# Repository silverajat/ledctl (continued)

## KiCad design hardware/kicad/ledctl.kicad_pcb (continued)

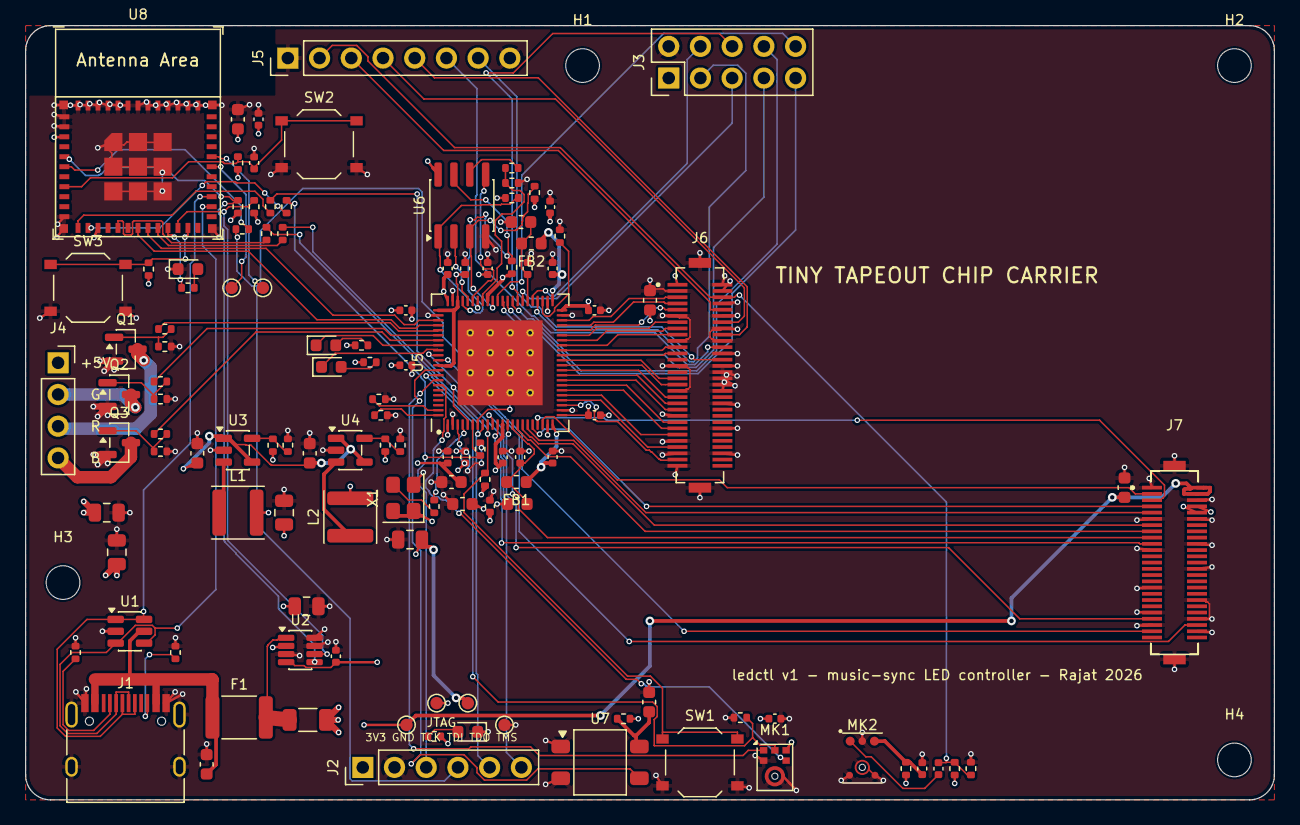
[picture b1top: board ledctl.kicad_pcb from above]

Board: 4 copper layers, 100.0 x 62.0 mm, 123 parts (0 on the bottom side), 112 nets.

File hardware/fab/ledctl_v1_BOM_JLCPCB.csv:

Comment,Designator,Footprint,LCSC Part #
10u,"C1,C4,C6,C34,C35,C36",C_0603_1608Metric,C19702
4.7k,"R9,R10,R18,R19,R20,R25,R26,R27,R35,R36",R_0402_1005Metric,C25900
22u,"C3,C5,C7,C28,C29",C_0805_2012Metric,C45783
ESP32-C3-MINI-1-N4,U8,ESP32-C3-MINI-1,C2838502
100n,"C2,C9,C11,C12,C13,C14,C15,C17,C18,C19,C20,C21,C22,C23,C24,C26,C27,C30,C37",C_0402_1005Metric,C1525
100k,R28,R_0402_1005Metric,C25741
4.7u,"C8,C10,C16,C25,C31",C_0603_1608Metric,C19666
button TS-1187A,"SW1,SW2,SW3",SW_Push_1P1T_XKB_TS-1187A,C318884
USB-C (power + ESP32 USB),J1,USB_C_Receptacle_HRO_TYPE-C-31-M-12,C165948
0,R16,R_0402_1005Metric,C17168
10k,"R7,R13,R33,R34",R_0402_1005Metric,C25744
68k,R5,R_0402_1005Metric,C36871
1k,"R11,R12,R14,R15,R17,R42",R_0402_1005Metric,C11702
100,"R22,R23,R24,R29,R30,R37,R38,R39,R40,R41",R_0402_1005Metric,C25076
10m 1%,R3,R_1206_3216Metric,C601097
600R@100MHz,"FB1,FB2",L_0603_1608Metric,C1002
"LED strip (1=+5V black, 2=G, 3=R, 4=B)",J4,PinSocket_1x04_P2.54mm_Vertical,C2718488
USBLC6-2SC6,U1,SOT-23-6,C7519
SY8089AAAC,"U3,U4",SOT-23-5,C78988
AO3400A,"Q1,Q2,Q3",SOT-23,C20917
IRM-H638T/TR2,U7,Everlight_IRM-H6xxT,C91447
2.2k,R4,R_0402_1005Metric,C25879
1u,"C32,C33,C38",C_0402_1005Metric,C52923
MSM381A3729Z9E-C,MK2,MEMSensing_LGA-6_2.95x3.76mm,C51928206
2.2uH SWPA4030S2R2MT,"L1,L2",L_Sunlord_SWPA4030S,C36409
22,R21,R_0402_1005Metric,C25092
FPGA JTAG,J2,PinHeader_1x06_P2.54mm_Vertical,C42431790
W25Q16JVSNIQ,U6,SOIC-8_3.9x4.9mm_P1.27mm,C2456211
27MHz 3.3V CMOS,X1,Oscillator_SMD_Abracon_ASE-4Pin_3.2x2.5mm,C22434870
5.1k,"R1,R2",R_0402_1005Metric,C25905
INA219AIDCNR,U2,SOT-23-8,C87469
GW2AR-LV18QN88C8/I7,U5,QFN-88-1EP_10x10mm_P0.4mm_EP6.74x6.74mm,C380550
DF12NB(5.0)-60DP-0.5V(51),J6,Hirose_DF12NB5.0-60DP_TT,C2847989
15k,"R6,R8",R_0402_1005Metric,C25756
DF12NB(5.0)-50DP-0.5V(51),J7,Hirose_DF12NB5.0-50DP_TT,C3020266
2.6A hold / 5A trip,F1,Fuse_1812_4532Metric,C20814
ICS-43434,MK1,InvenSense_ICS-43434-6_3.5x2.65mm,C5656610
red LED KT-0603R,"D1,D2,D3,D4",LED_0603_1608Metric,C2286

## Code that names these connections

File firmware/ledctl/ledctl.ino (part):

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// FPGA does the I2S mic + beat detection and sends 'B' on every beat.
//
// Pins (ESP32-C3-MINI-1):
//   GPIO4 = UART TX -> FPGA pin 70      GPIO5 = UART RX <- FPGA pin 69
//   GPIO8 = I2C SDA, GPIO2 = I2C SCL   (INA219 @0x40, 10 mOhm shunt -> 1 mA / LSB)
//   GPIO7 = status LED
//   GPIO0/1/3/10 = FPGA JTAG, GPIO6 = FPGA RECONFIG  -> never touched here
//
// UART frame to FPGA: 0xA5, cmd, a, b, c
//   'C' r g b   base colour      'M' mode (0 static, 1 music, 2 chill, 3 off)
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
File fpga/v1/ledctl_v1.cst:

IO_LOC "clk" 4;
IO_PORT "clk" IO_TYPE=LVCMOS33 PULL_MODE=UP;
IO_LOC "uart_rx" 70;
IO_PORT "uart_rx" IO_TYPE=LVCMOS33 PULL_MODE=UP;
IO_LOC "uart_tx" 69;
IO_PORT "uart_tx" IO_TYPE=LVCMOS33 DRIVE=8;
IO_LOC "i2s_sck" 82;
IO_PORT "i2s_sck" IO_TYPE=LVCMOS33 DRIVE=8;
IO_LOC "i2s_ws" 81;
IO_PORT "i2s_ws" IO_TYPE=LVCMOS33 DRIVE=8;
IO_LOC "i2s_sd" 80;
IO_PORT "i2s_sd" IO_TYPE=LVCMOS33 PULL_MODE=NONE;
IO_LOC "pwm_r" 71;
IO_PORT "pwm_r" IO_TYPE=LVCMOS33 DRIVE=8;
IO_LOC "pwm_g" 72;
IO_PORT "pwm_g" IO_TYPE=LVCMOS33 DRIVE=8;
IO_LOC "pwm_b" 73;
IO_PORT "pwm_b" IO_TYPE=LVCMOS33 DRIVE=8;
IO_LOC "led0_n" 74;
IO_PORT "led0_n" IO_TYPE=LVCMOS33 DRIVE=8;
IO_LOC "led1_n" 75;
IO_PORT "led1_n" IO_TYPE=LVCMOS33 DRIVE=8;
